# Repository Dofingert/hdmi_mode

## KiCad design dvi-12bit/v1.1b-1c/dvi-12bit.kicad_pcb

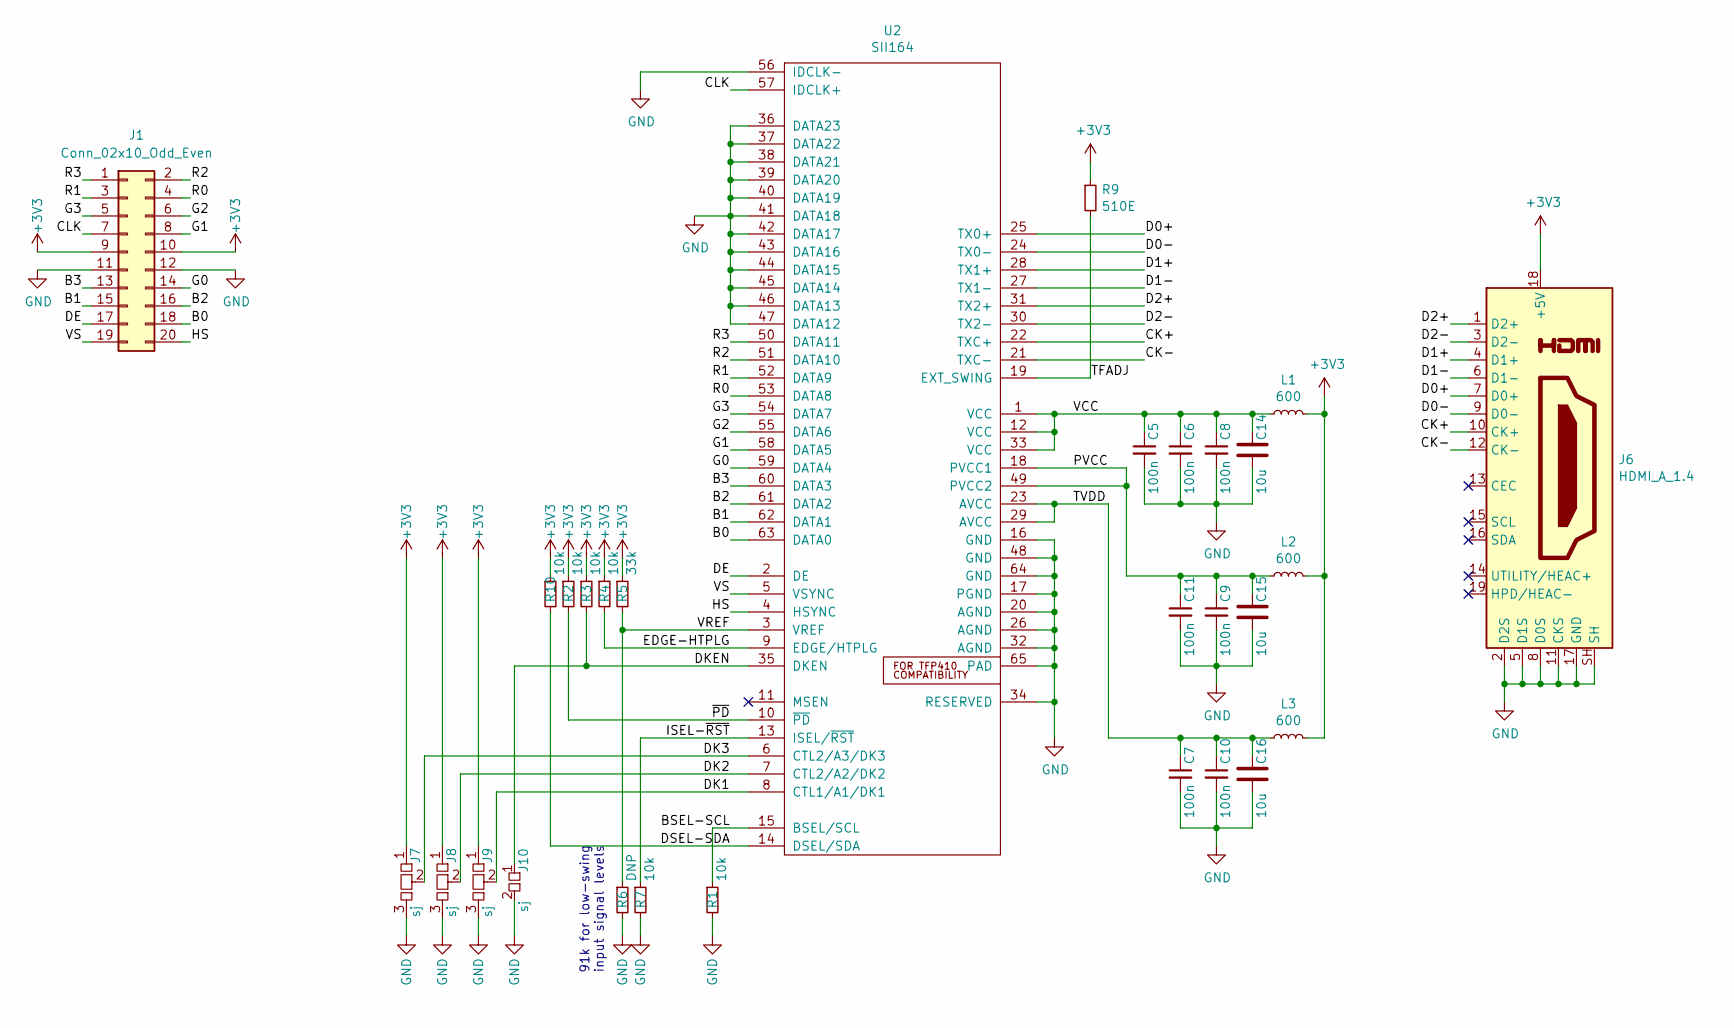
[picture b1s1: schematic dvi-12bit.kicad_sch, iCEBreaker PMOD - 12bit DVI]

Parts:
C5, C6, C7, C8, C9, C10, C11: 100n; C_0402
C14, C15, C16: 10u; C_0603
J1: Conn_02x10_Odd_Even; PinSocket_2.54mm_Nose
J6: HDMI_A_1.4; HDMI-SMD_HDMI-001S
J7, J8, J9: sj; J_0903
J10: sj; J_0603
L1, L2, L3: 600; L_0402
R1, R2, R3, R4, R7, R10: 10k; R_0402
R5: 33k; R_0402
R6: DNP; R_0402
R9: 510E; R_0402
U2: SII164; TQFP-64-1EP_10x10mm_P0.5mm_EP5x5mm

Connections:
+3V3: J1.9, J1.10, J6.18 (+5V), J7.1, J8.1, J9.1, L1.1, L2.1, L3.1, R2.1, R3.1, R4.1, R5.1, R9.1, R10.1
/B0: J1.18, U2.63 (DATA0)
/B1: J1.15, U2.62 (DATA1)
/B2: J1.16, U2.61 (DATA2)
/B3: J1.13, U2.60 (DATA3)
/BSEL-SCL: R1.1, U2.15 (BSEL/SCL)
/CK+: J6.10 (CK+), U2.22 (TXC+)
/CK-: J6.12 (CK-), U2.21 (TXC-)
/CLK: J1.7, U2.57 (IDCLK+)
/D0+: J6.7 (D0+), U2.25 (TX0+)
/D0-: J6.9 (D0-), U2.24 (TX0-)
/D1+: J6.4 (D1+), U2.28 (TX1+)
/D1-: J6.6 (D1-), U2.27 (TX1-)
/D2+: J6.1 (D2+), U2.31 (TX2+)
/D2-: J6.3 (D2-), U2.30 (TX2-)
/DE: J1.17, U2.2 (DE)
/DK1: J9.2, U2.8 (CTL1/A1/DK1)
/DK2: J8.2, U2.7 (CTL2/A2/DK2)
/DK3: J7.2, U2.6 (CTL2/A3/DK3)
/DKEN: J10.1, R3.2, U2.35 (DKEN)
/DSEL-SDA: R10.2, U2.14 (DSEL/SDA)
/EDGE-HTPLG: R4.2, U2.9 (EDGE/HTPLG)
/G0: J1.14, U2.59 (DATA4)
/G1: J1.8, U2.58 (DATA5)
/G2: J1.6, U2.55 (DATA6)
/G3: J1.5, U2.54 (DATA7)
/HS: J1.20, U2.4 (HSYNC)
/ISEL-~RST: R7.1, U2.13 (ISEL/~RST)
/PVCC: C9.1, C11.1, C15.1, L2.2, U2.18 (PVCC1), U2.49 (PVCC2)
/R0: J1.4, U2.53 (DATA8)
/R1: J1.3, U2.52 (DATA9)
/R2: J1.2, U2.51 (DATA10)
/R3: J1.1, U2.50 (DATA11)
/TFADJ: R9.2, U2.19 (EXT_SWING)
/TVDD: C7.1, C10.1, C16.1, L3.2, U2.23 (AVCC), U2.29 (AVCC)
/VCC: C5.1, C6.1, C8.1, C14.1, L1.2, U2.1 (VCC), U2.12 (VCC), U2.33 (VCC)
/VREF: R5.2, R6.1, U2.3 (VREF)
/VS: J1.19, U2.5 (VSYNC)
/~PD: R2.2, U2.10 (~PD)
GND: C5.2, C6.2, C7.2, C8.2, C9.2, C10.2, C11.2, C14.2, C15.2, C16.2, J1.11, J1.12, J6.2 (D2S), J6.5 (D1S), J6.8 (D0S), J6.11 (CKS), J6.17 (GND), J6.20, J6.21, J6.22, J6.23, J6.SH, J7.3, J8.3, J9.3, J10.2, R1.2, R6.2, R7.2, U2.16 (GND), U2.17 (PGND), U2.20 (AGND), U2.26 (AGND), U2.32 (AGND), U2.34 (RESERVED), U2.36 (DATA23), U2.37 (DATA22), U2.38 (DATA21), U2.39 (DATA20), U2.40 (DATA19), U2.41 (DATA18), U2.42 (DATA17), U2.43 (DATA16), U2.44 (DATA15), U2.45 (DATA14), U2.46 (DATA13), U2.47 (DATA12), U2.48 (GND), U2.56 (IDCLK-), U2.64 (GND), U2.65 (PAD)

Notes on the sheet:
91k for low-swing input signal levels

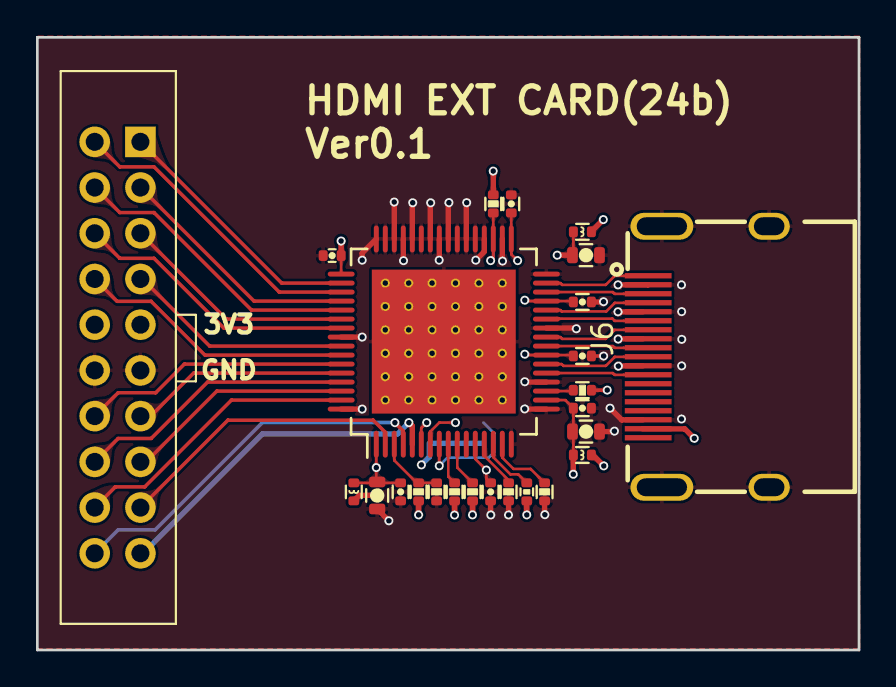
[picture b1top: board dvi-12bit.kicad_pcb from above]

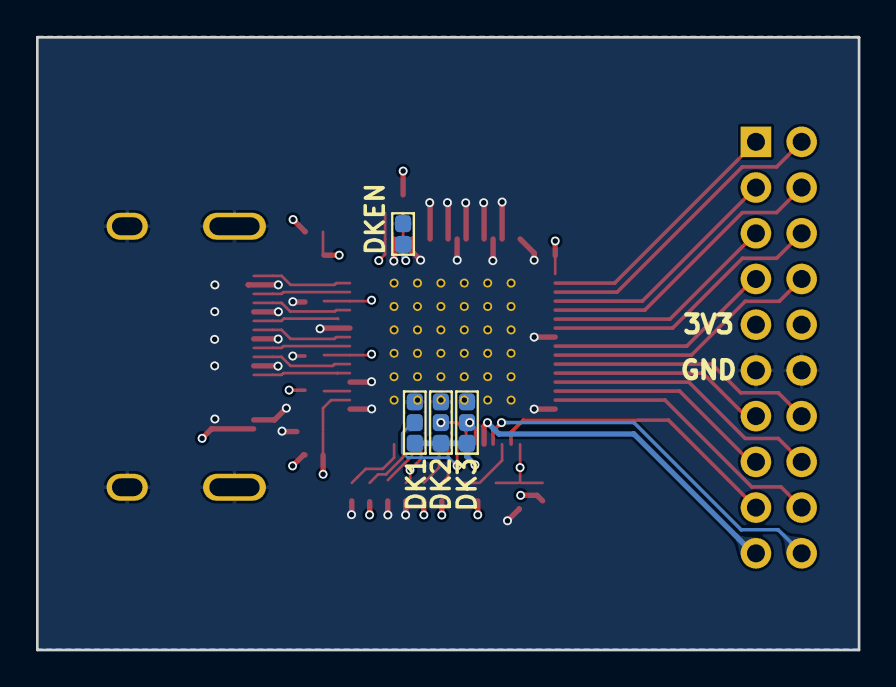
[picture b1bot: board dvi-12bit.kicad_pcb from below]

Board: 4 copper layers, 45.6 x 34.0 mm, 29 parts (4 on the bottom side), 40 nets.

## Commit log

2023-11-12 添加针对 BaiXin 开发板设计的 HDMI 输出模块
2023-11-13 Version 0.1

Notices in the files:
dvi-12bit/v1.1b-1c/dvi-12bit.kicad_pcb:
(C) 2018-2021 Piotr Esden-Tempski
(C) 2018-2021 1BitSquared
License: CC-BY-SA V4.0
